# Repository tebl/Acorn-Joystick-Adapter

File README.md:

# Acorn Joystick Adapter

I've been spending a lot of time restoring an old Acorn BBC Micro Model B, which mostly means fixing it up just enough to allow me to play all the entirely "unique" hits I've missed like _Repton_ and _Snapper_. As much fun as those games are, I grew up with a Commodore 64 so using the keyboard for everything seemed slightly more manual that I'd like so the next step was figuring out how to get and maintain a Joystick setup for the system.

These joysticks have however started to get more rare than the systems themselves, guessing it's the combination of a machine associated with school and the option to only provide analog inputs that have colluded to make them rarer than a Dodo. Also, the analog joysticks never did work all that great with just about any system I ever tried them with. So, let's go with something that is still somewhat actively produced; the good old Atari compatible joystick!

The circuit needed to convert from the micro-switched Atari joystick to the analog signals needed by the BBC Micro was on print in the may issue of BBC Micro User from 1983 (see gallery section for scans I found somewhere and ended up finding in my downloads-folder), thankfully it goes in great detail on how the various circuits work. Regrettably I failed at deciphering them completely, but found an easier to understand schematic over at [ZX Jims blog](http://zxjim.blogspot.com/2012/05/acorn-bbc-atari-joystick-adapter.html). With this as a starting point I plugged everything into KiCad and the result was a neat little PCB that can be ordered and assembled by just about everyone with a sensible set of soldering tools.

Rumours have it that the circuit could also be used to connect joysticks to an Acorn Electron with the Plus One expansion, but unless someone donates one of them to me that'll have to be a question for the ages.

# Schematic
The supplied KiCad files should be sufficient as both a schematic and as a  starting point for ordering PCBs (basically you could just zip the contents of the export folder and upload that on a fabrication site), the schematic is also available in [PDF-format](https://github.com/tebl/Acorn-Joystick-Adapter/raw/master/export/Acorn%20Joystick%20Adapter.pdf) and this is what you'll need to print and work your way through this things don't work as expected after assembly.

# BOM
Most parts should be easy to get a hold of from your favourite local electronic component shop though you might have to consider other sources for the older parts such as the CPU and memory. Personally I bought most components with free shipping from China via AliExpress - prices will vary, but I found everything in larger quantities than needed for the cost of a few cups of fancy coffee! 

Values in parenthesis is the component amounts that could be considered optional, for this specific build you'd probably only need the required components unless you intend to play the games together with someone special (aren't all Acorn fans?).

| Reference               | Item                                   | Count |
| ----------------------- | -------------------------------------- | ----- |
| PCB                     | Fabricate using Gerber files ([order](https://www.pcbway.com/project/shareproject/Acorn_Joystick_Adapter__Revision_A_.html?inviteid=88707))  |     1 |
| J1                      | DB15 male connector, PCB mount         |     1 |
| J2,J3                   | DB9 male connector (2 rows), PCB mount |     1 |
| J3                      | DB9 male connector (2 rows), PCB mount |   (1) |
| J4                      | 1x06 pin header                        |   (1) |
| Q1-Q3                   | BC337 transistor (TO-92)               |     3 |
| Q3-Q6                   | BC337 transistor (TO-92)               |   (3) |
| R1,R3,R5,R8,R10         | 10k ohm resistor                       |    5  |
| R12,R14,R16,R19,R21     | 10k ohm resistor                       |   (5) |
| R2,R4,R6,R7,R9,R11      | 20k ohm resistor                       |    5  |
| R13,R15,R17,R18,R20,R22 | 20k ohm resistor                       |  (5)  |

Please use the order link above when signing up to help me support this project, I'll get a small discount on future orders and hopefully that means I can afford to keep developing new and exciting modules in the future. By using the URL you won't have to deal with the rather daunting order forms for PCB fabrication, but if you want to go that route they'll probably want a zipped-up copy of the files in the export-directory!

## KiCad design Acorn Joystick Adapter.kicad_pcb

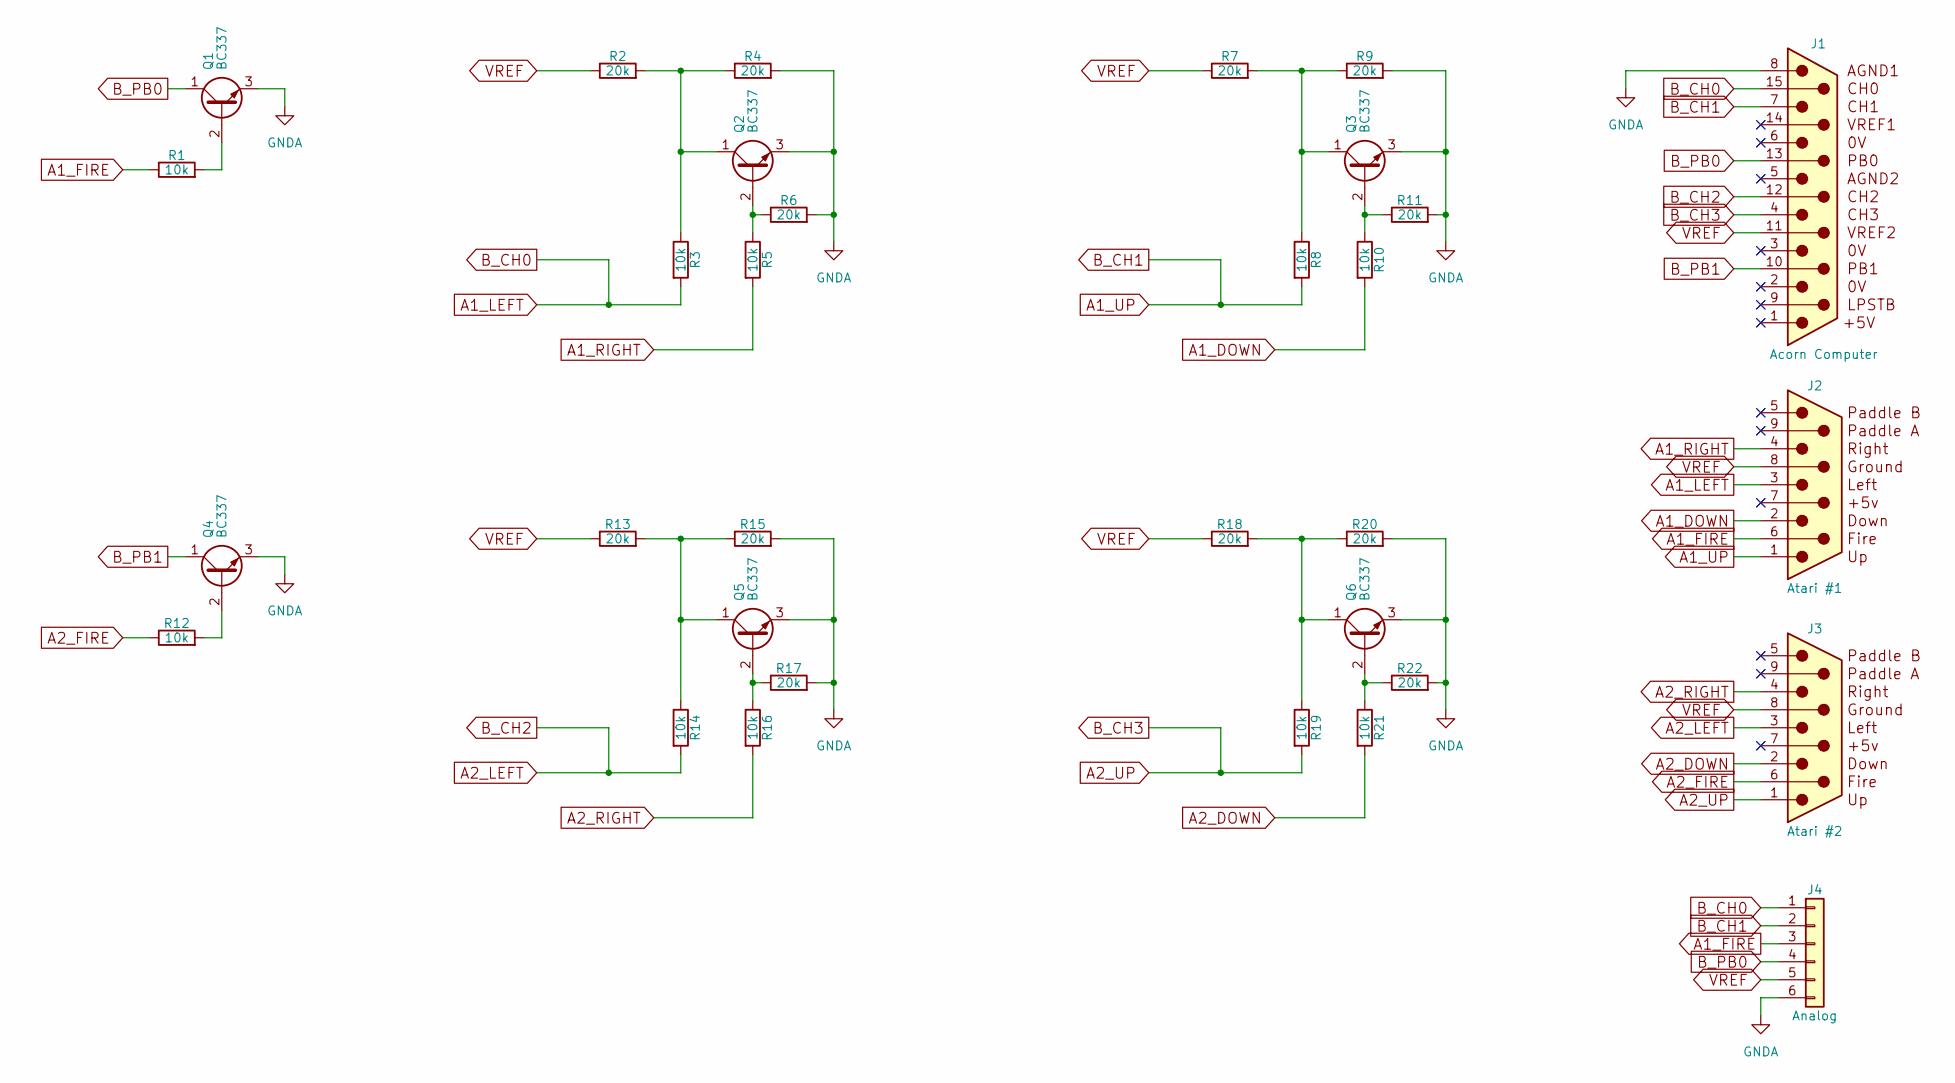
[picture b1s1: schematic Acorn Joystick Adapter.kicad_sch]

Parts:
J1: Acorn Computer; DSUB-15_Male_Vertical_Pitch2.77x2.84mm
J2: Atari #1; DSUB-9_Male_Vertical_Pitch2.77x2.84mm
J3: Atari #2; DSUB-9_Male_Vertical_Pitch2.77x2.84mm
J4: Analog; PinHeader_1x06_P2.54mm_Vertical
Q1, Q2, Q3, Q4, Q5, Q6: BC337; TO-92_Inline_Wide
R1, R3, R5, R8, R10, R12, R14, R16, R19, R21: 10k; R_Axial_DIN0207_L6.3mm_D2.5mm_P10.16mm_Horizontal
R2, R4, R6, R7, R9, R11, R13, R15, R17, R18, R20, R22: 20k; R_Axial_DIN0207_L6.3mm_D2.5mm_P10.16mm_Horizontal

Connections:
A1_DOWN: J2.2, R10.2
A1_FIRE: J2.6, J4.3, R1.1
A1_LEFT: J1.15, J2.3, J4.1, R3.2
A1_RIGHT: J2.4, R5.2
A1_UP: J1.7, J2.1, J4.2, R8.2
A2_DOWN: J3.2, R21.2
A2_FIRE: J3.6, R12.1
A2_LEFT: J1.12, J3.3, R14.2
A2_RIGHT: J3.4, R16.2
A2_UP: J1.4, J3.1, R19.2
B_PB0: J1.13, J4.4, Q1.1 (C)
B_PB1: J1.10, Q4.1 (C)
GNDA: J1.8, J4.6, Q1.3 (E), Q2.3 (E), Q3.3 (E), Q4.3 (E), Q5.3 (E), Q6.3 (E), R4.2, R6.2, R9.2, R11.2, R15.2, R17.2, R20.2, R22.2
unnamed: Q1.2 (B), R1.2
unnamed: Q2.2 (B), R5.1, R6.1
unnamed: Q2.1 (C), R2.2, R3.1, R4.1
unnamed: Q3.2 (B), R10.1, R11.1
unnamed: Q3.1 (C), R7.2, R8.1, R9.1
unnamed: Q4.2 (B), R12.2
unnamed: Q5.2 (B), R16.1, R17.1
unnamed: Q5.1 (C), R13.2, R14.1, R15.1
unnamed: Q6.2 (B), R21.1, R22.1
unnamed: Q6.1 (C), R18.2, R19.1, R20.1
VREF: J1.11 (P111), J2.8, J3.8, J4.5, R2.1, R7.1, R13.1, R18.1

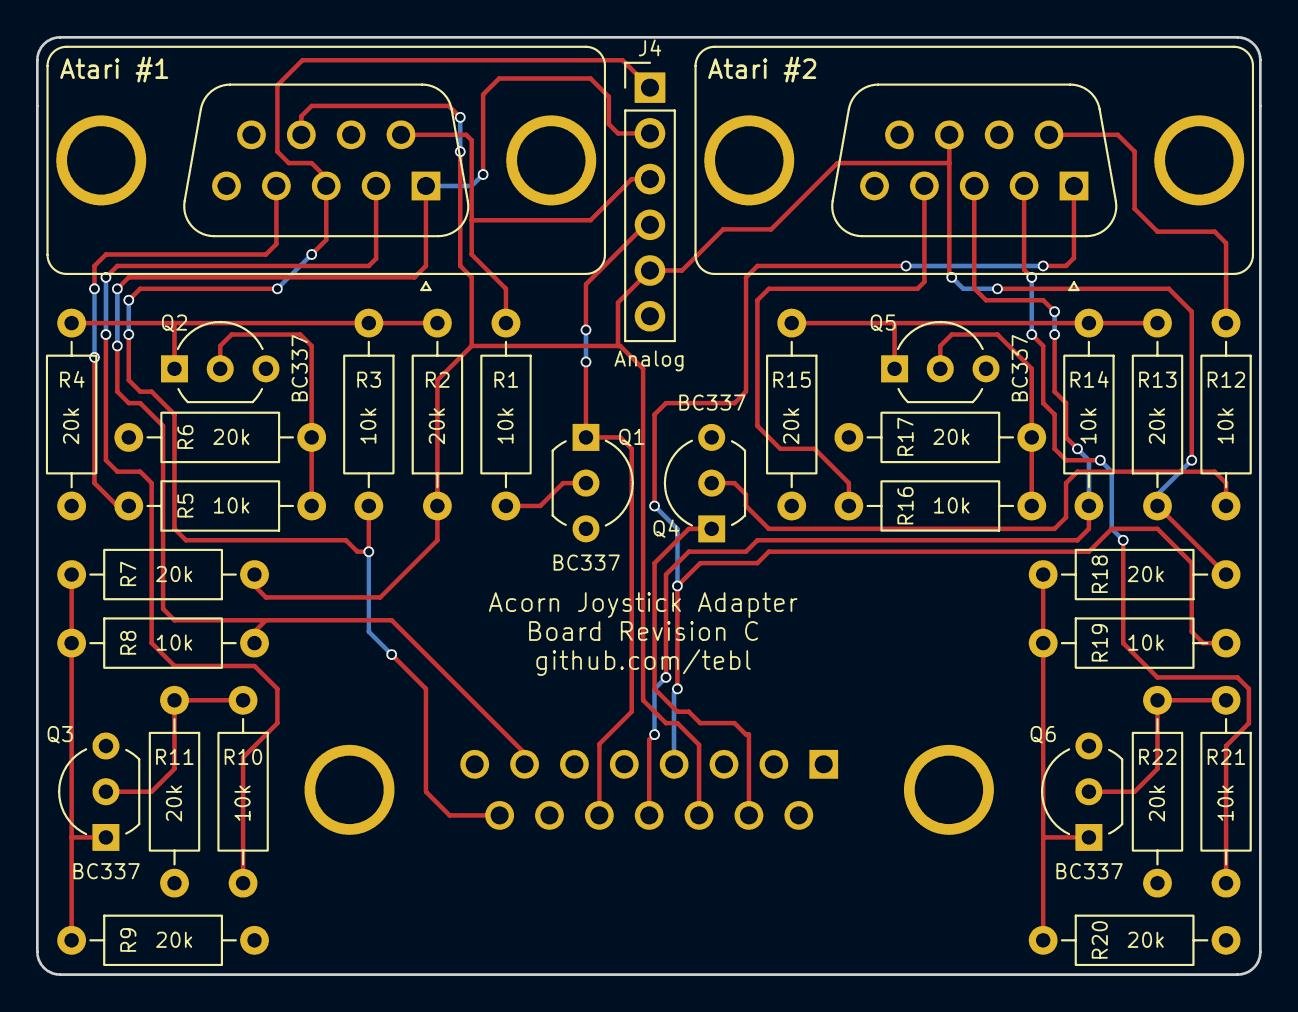
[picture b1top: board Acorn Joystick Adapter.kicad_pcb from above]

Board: 2 copper layers, 67.9 x 52.1 mm, 32 parts (1 on the bottom side), 24 nets.

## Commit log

2018-09-23 Blank project
2018-09-23 Basic schematic
2018-09-25 Single port, second as placeholder
2018-09-29 Added second joystick port to schematic
2018-09-30 Changed transistor footprint and pcb layout
2018-09-30 Resized board to match plastic enclosure height
2018-09-30 Gerber export
2018-09-30 Added analog breakout header
2018-10-17 Changed transistor footprint (easier to solder)
2018-10-17 Rotated atari connectors so 90 degree ones can be used
2018-10-17 Smaller DSUB mounting holes
2018-10-17 Updated schematic pdf
2018-10-18 Added README
2025-12-06 Upgrade schematic to new KiCAD
2025-12-07 Updated project for recent version of KiCAD
